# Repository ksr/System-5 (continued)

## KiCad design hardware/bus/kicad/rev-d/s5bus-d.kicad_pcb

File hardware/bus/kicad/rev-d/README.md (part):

# System-5 bus backplane Rev D (S5BUS-D): KiCad master

A fresh backplane (2026-10-26), derived from the cards that plug in and from the board Ken built in 2009
(`../rev-2009/`, six 36-pin slots). Generated by `gen/` from one netlist (`gen/netlist.py`): `gen/make_schematic.py`
writes the schematic, `gen/make_board.py` the board; Freerouting routes what the generator does not lay itself.

**Not ordered.** Before any order: `~/Developer/pcb-check/pcb-check hardware/bus/kicad/rev-d/s5bus-d.kicad_pcb hardware/bus/kicad/rev-d/s5bus-d-gerbers.zip --layers 2` must show no FAIL (Ken's check for every system since 2026-11-06; `hardware/BUILD-RULES.md`, section 2). **Power redone on 2026-11-18** (Ken: "simplify bus power"): a barrel jack for any 7–15 V adapter, a Schottky against a reversed plug, the power switch and a 3 A switching regulator, no fuse, in place of the screw terminal for a 5 V supply, the polyfuse and the P-MOSFET; the values of C2-C9 on the silkscreen (`pcb-check`'s one warning of 2026-11-16 and 17). Built by `gen/build.sh` (schematic, ERC, board, Freerouting on a fixed-order input, DRC, order files, `tools/preorder_check.py`): every build gives the same tracks. Since then: `tools/preorder_check.py --layers 2` PASS (DRC 0 errors and 0 warnings, the netlist proof 40 of 40); `pcb-check --tests` with `pcb-check.ini` (all eight slots against the bus definition; the bring-up tests) at elf `c2e90ac`: **no failures, 0 warnings**. **Then an external 5 V option** (Ken, the same evening): J10, two screw terminals for a regulated 5 V supply, and JP1, one jumper picking the source (REG or EXT), with the power switch after it for either source; `tools/preorder_check.py --layers 2` PASS (DRC 0 errors and 0 warnings, the netlist proof 42 of 42) and `pcb-check --tests` at elf `709855c`: **no failures, 0 warnings**. **Then, still on 2026-11-18, the slot and the board** (Ken): the 30-pin bus flush with each slot's GND end, the six extra lines beyond +5V, and the slot counted from GND ("The slot" below); RN2 9 mm further from slot 1's socket; 1.25 in between slots 7 and 8; the power switch a Marquardt 9070-1W, YACC1's RESET/RUN model; 2 mm more height at the GND end, 244.35 × 116 mm; `s5bus-d-1to1.pdf`. `tools/preorder_check.py --layers 2` PASS and `pcb-check --tests` at elf `31c54a8` (pcb-check `60fd275`, 2026-11-18): **no failures, 0 warnings** (the bus pins of all eight slots as defined, 288; 244.5 × 116.1 mm, 8 mounting holes; the bring-up tests pass). **Then the power switch again** (Ken, the same evening): an M9040P, the upright toggle of the IO panel's data switches, in place of the 9070-1W ("Circuit", SW1, with what is known of its rating); the supply feeds 2.0 mm into it again. `tools/preorder_check.py --layers 2` PASS (DRC 0 errors and 0 warnings, 0 unconnected, the netlist proof 42 of 42; routing seed 0) and `pcb-check --tests` at elf `4b24853` (2026-11-18, by the pcb-check session): **no failures, 0 warnings**. **Then, 2026-11-19, SW1's body on the fab layer at full size** (Ken: "yes draw the toggle outline full size"; a drawing only: no pad, label or track changed, the copper and the silkscreen checked the same): `tools/preorder_check.py --layers 2` PASS and `pcb-check --tests` at elf `e5322e4` (pcb-check `f93259d`): **no failures, 0 warnings**, every text clear of the parts with the toggle at its true size. SW1's part number is still to be read off the switch that will be fitted, for its rating ("Circuit", SW1).

## Ken's choices (2026-10-26)

| Choice | Decision |
|---|---|
| Pins per slot | **36**, as 2009. Since 2026-11-18 the 30-pin bus ends at the slot's end pin, GND, and a 30-pin card plugs in flush with that end (below); until then it took the middle 30, as on the 2009 board |
| Slots | **8** (CPU, memory, 6845, IO, IDE, bus driver, two spare) |
| Slot spacing (2026-11-18) | **1.0 in (25.4 mm)**, as 2009, **but 1.25 in (31.75 mm) between slots 7 and 8**, the two farthest from the power connector (Ken: "only that one space"): slot 8's card has 27.6 mm for its components instead of 21.3 (the board 6.35 mm wider, 244.35 mm) |
| Height (2026-11-18) | **116 mm**, 2 mm more at the GND end (Ken), so a 30-pin card plugged in flush with that end stays over the board |
| Power (2026-11-18) | **a centre-positive barrel jack for any 7–15 V adapter, a Schottky diode against a reversed plug, the power switch, a 3 A switching regulator to 5 V, the power LED; no fuse** (Ken: "simplify bus power"). Until then: a screw terminal for a 5 V supply and no regulator, as built in 2009 |
| External 5 V (2026-11-18) | **or an external regulated 5 V supply on two screw terminals (J10), the source picked by one 3-pin jumper (JP1): REG, the regulator, or EXT, J10; the power switch after the jumper, so it switches either source** (Ken: "add an option that 5V can also come from an external regulated supply. Add jumpers to select source"; "External 5V will come in via 2 screw terminals"; his choices: one 3-pin jumper, whose single shunt cannot join the two supplies, and the switch after it) |
| Pull-ups | 10k on D0–D7 and on the open-collector lines -EF, -EF1–3, -PAUSE, -DMAIN; -INT and -RESET added 2026-10-31 |
| Idle states (2026-11-01) | 10k pull-downs on N0–N2, TPA, TPB and pull-ups on -VMA, -MRD, -MRW: with no master on the bus, no I/O port is selected, no strobe is active and no card drives the data lines or writes memory |
| Mounting holes | 8 × M3, **four along each long edge**, between slots |
| Review fixes (2026-10-26) | copper keep-outs at the holes, 2.5 mm supply feeds, a card-window bracket on each slot (below) |
| After the independent reviews (2026-10-27) | a 5 A power switch (E-Switch 100 series, right-angle), a 4 A polyfuse and a P-channel MOSFET for reverse-polarity protection (both gone with the barrel jack, 2026-11-18), C1 in a 6.3 mm can, 1.0 mm silkscreen text, separate PTH / NPTH drill files |

## The slot

Pins are numbered by position along the 36-pin socket, **counted from the GND end** (the socket itself is an unnumbered
strip: the numbers are the drawings', and each socket's footprint is turned so that its pin 1 is that end). **The order
since 2026-11-18** (Ken: "looking at the bus from the power supply end I want the right most pin to be gnd followed by
the next original pin order all the way to +5v/vcc, then EF1, EF2, EF3, -DMAin, SC0", -PAUSE kept, at the far end; and
"start counting at gnd as pin 1, there +5v is 30 and then the pins beyond 5v"):

| Positions | Lines |
|---|---|
| 1–30 | the 30-pin System-5 bus from its GND end: GND at 1, the end pin (the rightmost, seen from the power connector), N0 2, N1 3, -RESET 4, -VMA 5, -EF 6, N2 7, -INT 8, A7–A0 at 9–16, -MRW 17, -MRD 18, TPB 19, TPA 20, Q 21, D7–D0 at 22–29, +5V at 30. A 30-pin card's own pin *n* (+5V 1 … GND 30) is position 31 − *n* |
| 31–33 | -EF1, -EF2, -EF3 (-EF1 next to +5V) |
| 34–36 | -DMAIN, SC0, -PAUSE (-PAUSE at the far end: the leftmost, seen from the power connector) |

A 30-pin card plugs into positions 1–30, flush with the GND end. Until 2026-11-18 the slot was counted from the other
end, in the 2009 board's order: 1–3 -EF1, -EF2, -EF3, 4–33 the 30-pin bus (+5V at 4, GND at 33), 34–36 -PAUSE, -DMAIN,
SC0 (the 2009 drawing's -INP, -OUT, EXP), the 30-pin bus in the middle. So a 36-pin card for this order (CPU Rev D, the
IO panel, BUSDRV-C) **does not fit the 2009 backplane**: there its +5V pin would meet D2. A 30-pin card fits both. The
2009 board's Eagle pin numbers differ too (1–30 the bus, 31–33 -EF1–3, 34–36 the rest), and its copper wired -EF1 next
to +5V, as here now, although its silkscreen says -EF3. The bus lines themselves, the pull-ups and the slots' places
are as before: only which line runs along which row changed, with RN1 (in line with the +5V and D0–D7 rows) and the
card-window brackets, and RN3 and RN4 moved to make room for RN1.

## Circuit

| Part | What |
|---|---|
| J1–J8 | the slots: 36-pin single-row 0.1" sockets on a 1.0" (25.4 mm) pitch, as 2009, but slots 7 and 8 1.25" (31.75 mm) apart (Ken, 2026-11-18) |
| J9 | power in: a DC barrel jack, Same Sky (formerly CUI) **PJ-063AH** (right angle, 2.0 mm centre pin for the common 5.5 × 2.1 mm plug, 8 A, 24 V; Digi-Key and Mouser stock it), at the left edge with its opening flush with the edge. **Centre positive**, 7–15 V: a 9 V or 12 V adapter of 2 A or more is the usual choice (a 7 V one at most about 2 A of load: below). Pin 1 the centre pin, pin 2 the sleeve (GND); its two kinked support legs (MP) are soldered to GND. Labelled J9 POWER IN, 7-15V DC, CENTER + |
| D2 | reverse-polarity protection: a Schottky rectifier, Vishay **SB540-E3/54** (40 V, 5 A, DO-201AD; the onsemi SB540 is obsolete), in series from J9's centre pin, lying flat (5.3 mm body). A centre-negative plug leaves it reverse-biased, so nothing reaches C10, the regulator or the cards. It drops about 0.4 V at 2 A (about 0.8 W), which the regulator absorbs |
| C10 | 47 µF 35 V, 6.3 mm can, on the regulator's input side (after D2, so a reversed plug never reaches it): it damps the ring when an adapter is plugged in live, through its cable's inductance |
| SW1 | power switch: an **M9040P**, the upright Marquardt SPDT toggle of the IO panel's data switches and of the YACC1 IO card (Ken, 2026-11-18: "bus change on off switch to same toggle used on IO card data 1-8"; earlier that day a right-angle Marquardt 9070-1W, YACC1's RESET/RUN model, which a real switch fitted on the full-size print, and from 2026-10-27 an E-Switch 100 series). Footprint `s5bus.pretty/M9040P`, the IO panel's (the YACC1 IO card's, pad for pad): three oval pads 5.41 × 2.71 mm, 4.699 mm apart, 1.8 mm holes (its body's outline on the fab layer at full size since 2026-11-19, Ken: "yes draw the toggle outline full size"; until then that layer had only the sketch of the lever, 8.2 × 10.3 mm); a body of 8.6 × 13.4 mm standing on the board below J10, 10.9 mm in from the left edge, its lever moving along that edge. It follows the source jumper and switches whichever source JP1 picks: common (pin 2) from JP1's middle pin; pin 3 to +5V = ON with the lever **up**, towards J9 (a toggle closes the contact on the side away from its lever: check against a real switch); pin 1 open = OFF. U1 runs whenever an adapter is in J9, the switch only cutting its output from the bus. Labelled ON, SW1 POWER and OFF beside it, each position level with the end its lever is at. **Its contact rating:** the whole bus current passes through it (up to 3 A from U1, or what J10's supply gives). Distributors list Marquardt's standard 9040-series toggles at 5 A 48 V AC and about 4 A 30 V DC, which covers it; the series' low-level (gold contact) versions are for 0.4 VA only and would not do. The data sheets themselves could not be read here on 2026-11-18: check the part number on the switch that is fitted |
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
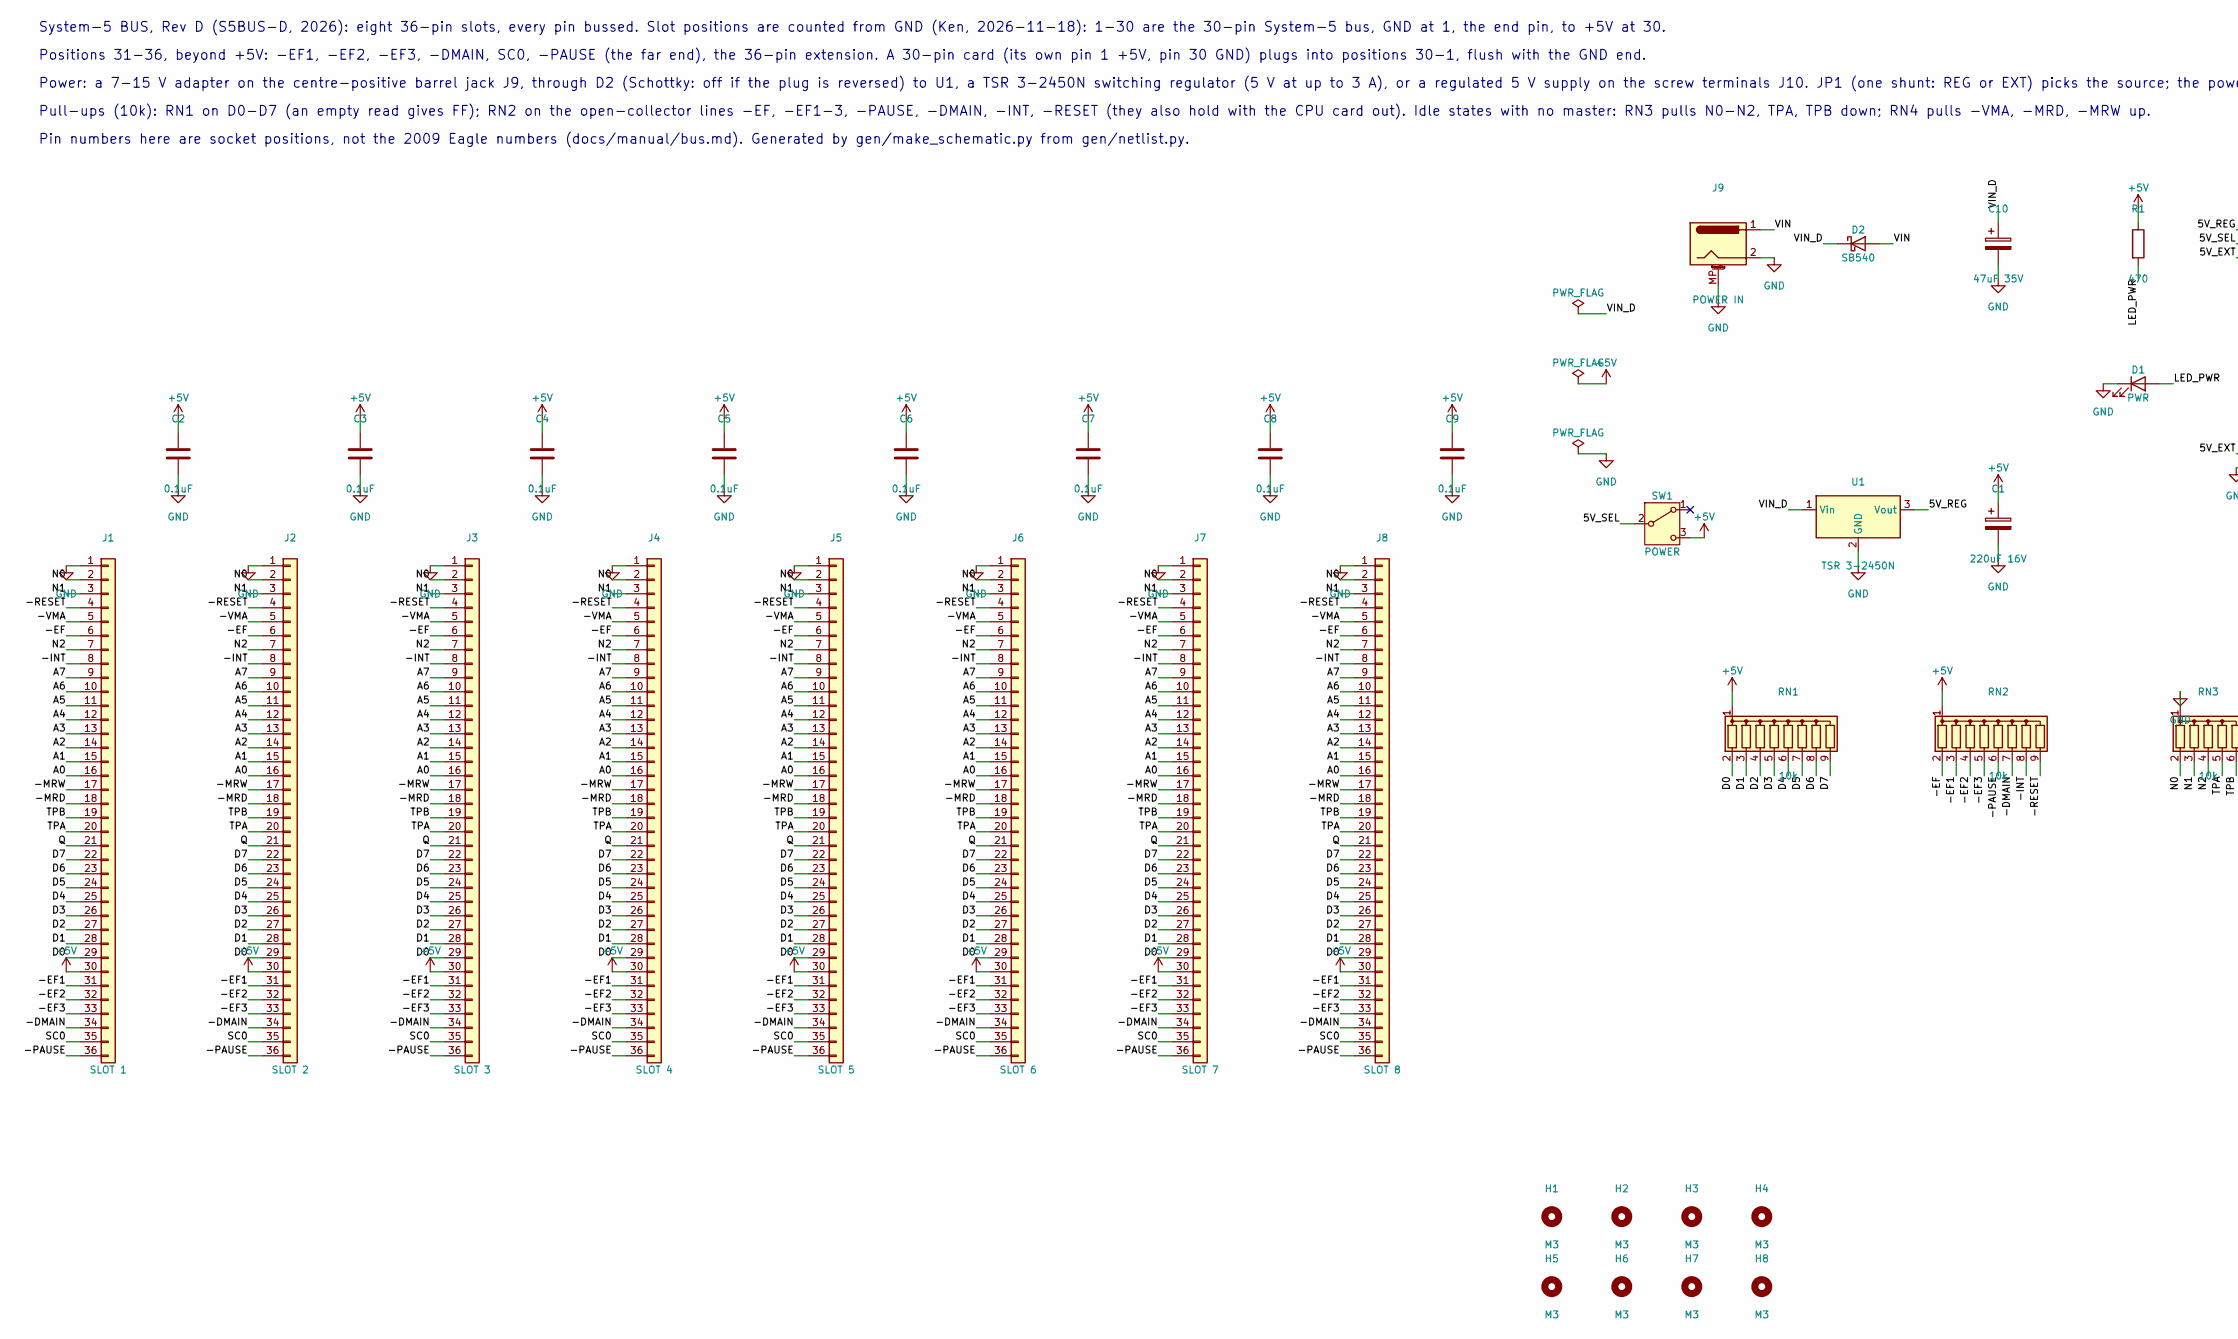
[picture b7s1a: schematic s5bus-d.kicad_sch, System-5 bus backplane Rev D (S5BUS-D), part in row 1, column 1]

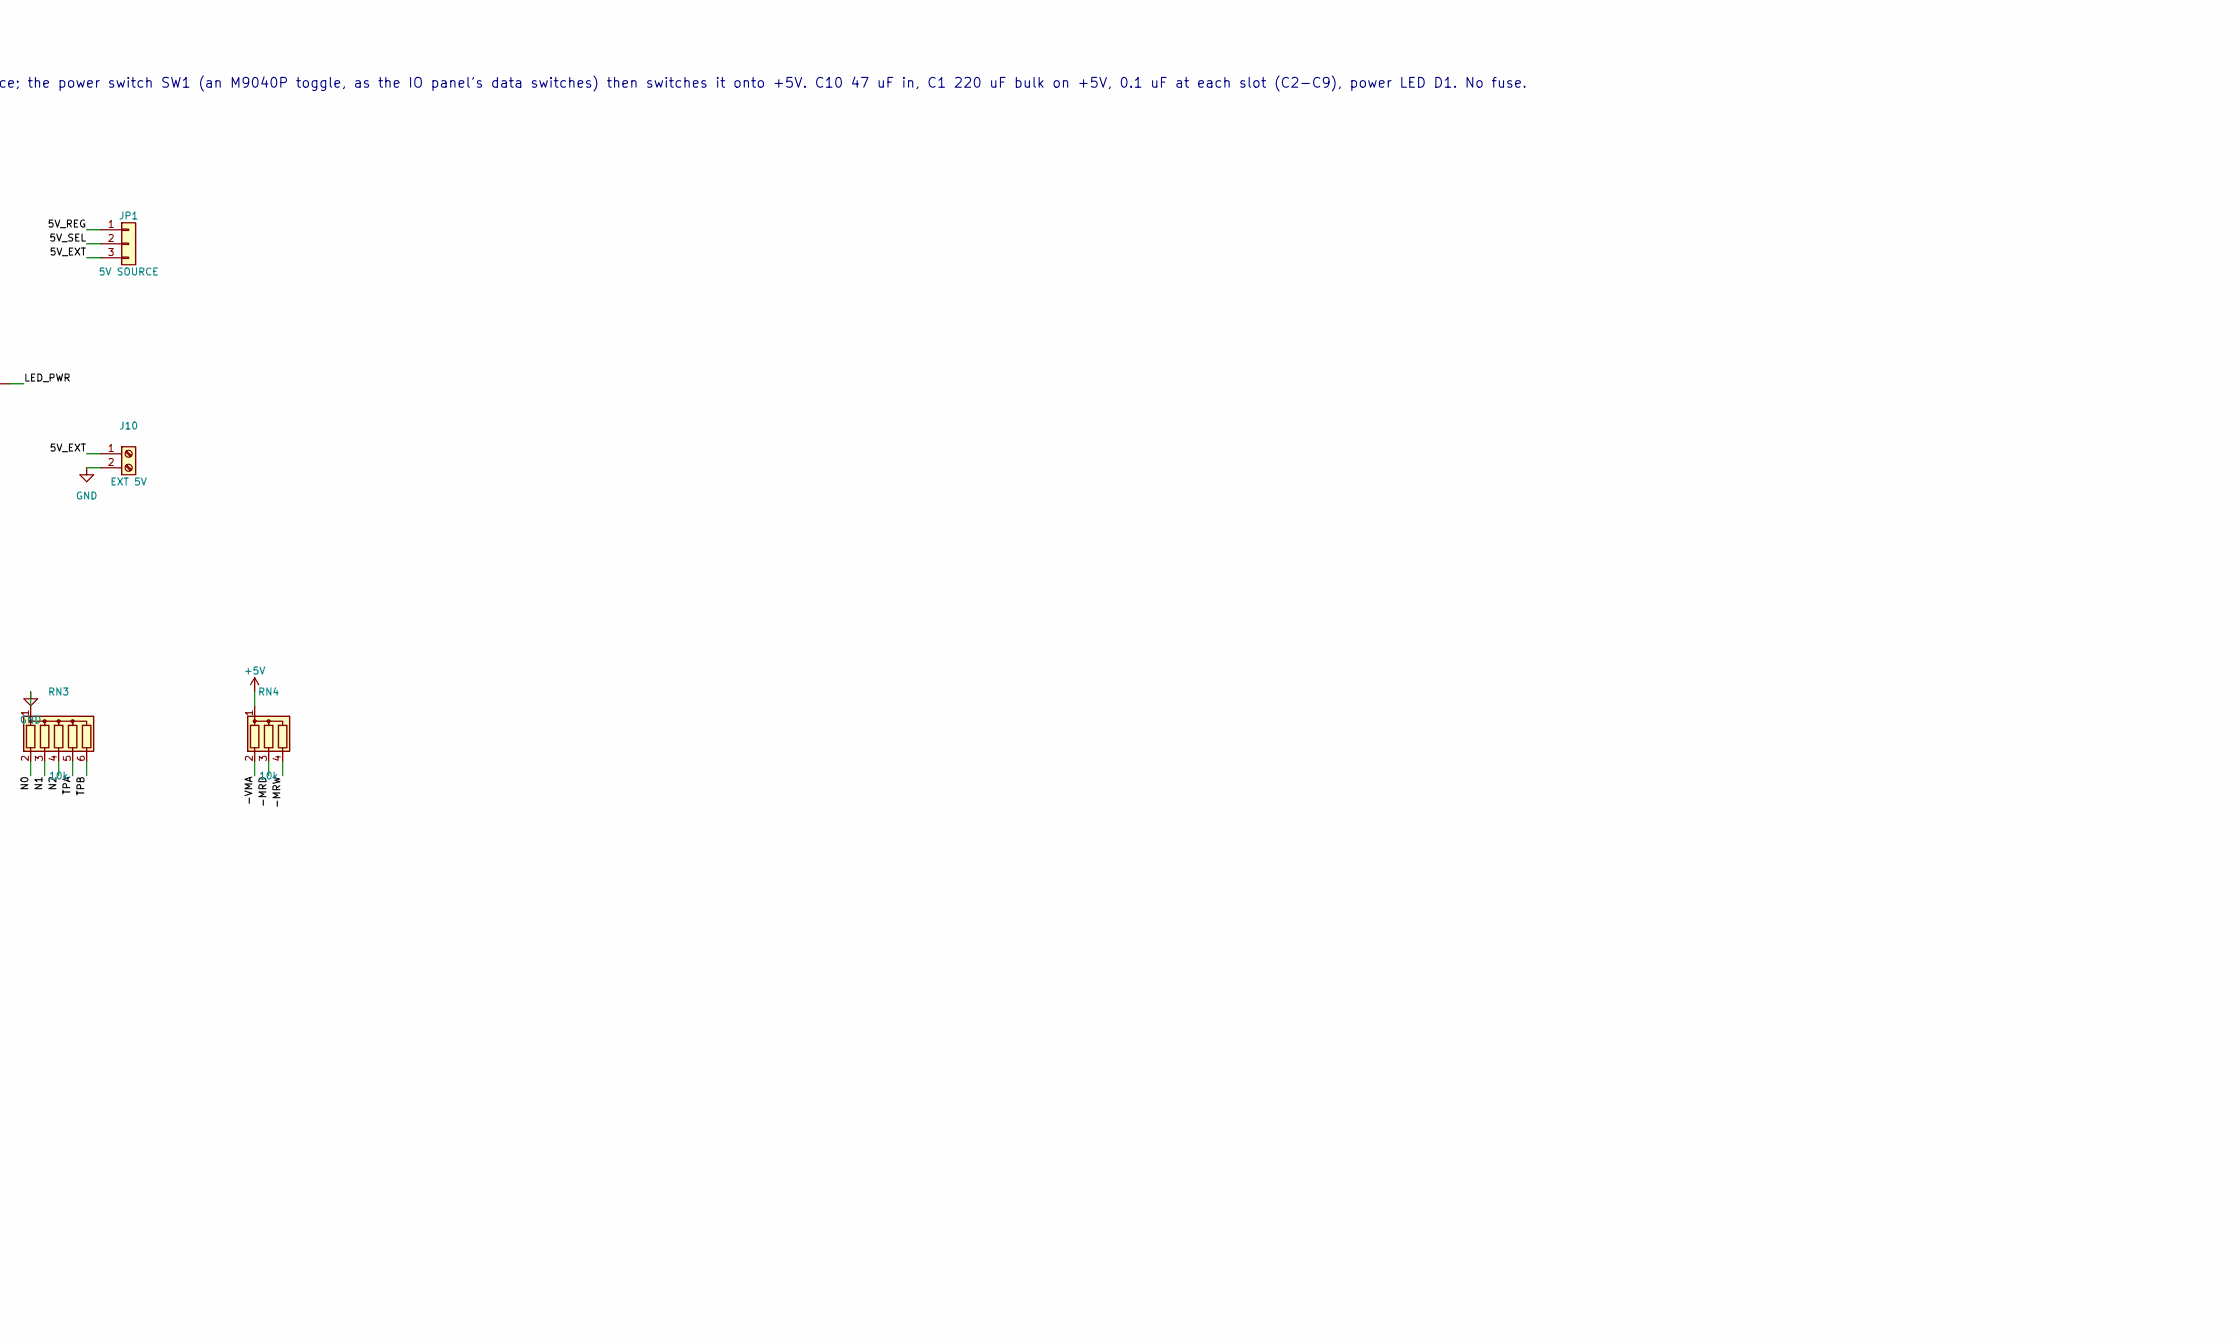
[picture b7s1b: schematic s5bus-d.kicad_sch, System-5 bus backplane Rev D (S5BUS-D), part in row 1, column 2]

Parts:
C1: 220uF 16V; CP_Radial_D6.3mm_P2.50mm
C2, C3, C4, C5, C6, C7, C8, C9: 0.1uF; C025-050X050
C10: 47uF 35V; CP_Radial_D6.3mm_P2.50mm
D1: PWR; LED_D5.0mm
D2: SB540; D_DO-201AD_P15.24mm_Horizontal
H1, H2, H3, H4, H5, H6, H7, H8: M3; MountingHole_3.2mm_M3
J1: SLOT 1; PinSocket_1x36_P2.54mm_Vertical
J2: SLOT 2; PinSocket_1x36_P2.54mm_Vertical
J3: SLOT 3; PinSocket_1x36_P2.54mm_Vertical
J4: SLOT 4; PinSocket_1x36_P2.54mm_Vertical
J5: SLOT 5; PinSocket_1x36_P2.54mm_Vertical
J6: SLOT 6; PinSocket_1x36_P2.54mm_Vertical
J7: SLOT 7; PinSocket_1x36_P2.54mm_Vertical
J8: SLOT 8; PinSocket_1x36_P2.54mm_Vertical
J9: POWER IN; BarrelJack_CUI_PJ-063AH_Horizontal
J10: EXT 5V; TerminalBlock_Phoenix_MKDS-1,5-2-5.08_1x02_P5.08mm_Horizont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
JP1: 5V SOURCE; PinHeader_1x03_P2.54mm_Vertical
R1: 470; R_Axial_DIN0207_L6.3mm_D2.5mm_P7.62mm_Horizontal
RN1, RN2: 10k; R_Array_SIP9
RN3: 10k; R_Array_SIP6
RN4: 10k; R_Array_SIP4
SW1: POWER; M9040P
U1: TSR 3-2450N; Converter_DCDC_TRACO_TSR2-24xxN_TSR2-24xxxN_THT

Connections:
+5V: C1.1, C2.1, C3.1, C4.1, C5.1, C6.1, C7.1, C8.1, C9.1, J1.30, J2.30, J3.30, J4.30, J5.30, J6.30, J7.30, J8.30, R1.1, RN1.1 (common), RN2.1 (common), RN4.1 (common), SW1.3 (C)
/5V_EXT: J10.1, JP1.3
/5V_REG: JP1.1, U1.3 (Vout)
/5V_SEL: JP1.2, SW1.2 (B)
/-DMAIN: J1.34, J2.34, J3.34, J4.34, J5.34, J6.34, J7.34, J8.34, RN2.7 (R6)
/-EF: J1.6, J2.6, J3.6, J4.6, J5.6, J6.6, J7.6, J8.6, RN2.2 (R1)
/-EF1: J1.31, J2.31, J3.31, J4.31, J5.31, J6.31, J7.31, J8.31, RN2.3 (R2)
/-EF2: J1.32, J2.32, J3.32, J4.32, J5.32, J6.32, J7.32, J8.32, RN2.4 (R3)
/-EF3: J1.33, J2.33, J3.33, J4.33, J5.33, J6.33, J7.33, J8.33, RN2.5 (R4)
/-INT: J1.8, J2.8, J3.8, J4.8, J5.8, J6.8, J7.8, J8.8, RN2.8 (R7)
/-MRD: J1.18, J2.18, J3.18, J4.18, J5.18, J6.18, J7.18, J8.18, RN4.3 (R2)
/-MRW: J1.17, J2.17, J3.17, J4.17, J5.17, J6.17, J7.17, J8.17, RN4.4 (R3)
/-PAUSE: J1.36, J2.36, J3.36, J4.36, J5.36, J6.36, J7.36, J8.36, RN2.6 (R5)
/-RESET: J1.4, J2.4, J3.4, J4.4, J5.4, J6.4, J7.4, J8.4, RN2.9 (R8)
/-VMA: J1.5, J2.5, J3.5, J4.5, J5.5, J6.5, J7.5, J8.5, RN4.2 (R1)
/A0: J1.16, J2.16, J3.16, J4.16, J5.16, J6.16, J7.16, J8.16
/A1: J1.15, J2.15, J3.15, J4.15, J5.15, J6.15, J7.15, J8.15
/A2: J1.14, J2.14, J3.14, J4.14, J5.14, J6.14, J7.14, J8.14
/A3: J1.13, J2.13, J3.13, J4.13, J5.13, J6.13, J7.13, J8.13
/A4: J1.12, J2.12, J3.12, J4.12, J5.12, J6.12, J7.12, J8.12
/A5: J1.11, J2.11, J3.11, J4.11, J5.11, J6.11, J7.11, J8.11
/A6: J1.10, J2.10, J3.10, J4.10, J5.10, J6.10, J7.10, J8.10
/A7: J1.9, J2.9, J3.9, J4.9, J5.9, J6.9, J7.9, J8.9
/D0: J1.29, J2.29, J3.29, J4.29, J5.29, J6.29, J7.29, J8.29, RN1.2 (R1)
/D1: J1.28, J2.28, J3.28, J4.28, J5.28, J6.28, J7.28, J8.28, RN1.3 (R2)
/D2: J1.27, J2.27, J3.27, J4.27, J5.27, J6.27, J7.27, J8.27, RN1.4 (R3)
/D3: J1.26, J2.26, J3.26, J4.26, J5.26, J6.26, J7.26, J8.26, RN1.5 (R4)
/D4: J1.25, J2.25, J3.25, J4.25, J5.25, J6.25, J7.25, J8.25, RN1.6 (R5)
/D5: J1.24, J2.24, J3.24, J4.24, J5.24, J6.24, J7.24, J8.24, RN1.7 (R6)
/D6: J1.23, J2.23, J3.23, J4.23, J5.23, J6.23, J7.23, J8.23, RN1.8 (R7)
/D7: J1.22, J2.22, J3.22, J4.22, J5.22, J6.22, J7.22, J8.22, RN1.9 (R8)
/LED_PWR: D1.2 (A), R1.2
/N0: J1.2, J2.2, J3.2, J4.2, J5.2, J6.2, J7.2, J8.2, RN3.2 (R1)
/N1: J1.3, J2.3, J3.3, J4.3, J5.3, J6.3, J7.3, J8.3, RN3.3 (R2)
/N2: J1.7, J2.7, J3.7, J4.7, J5.7, J6.7, J7.7, J8.7, RN3.4 (R3)
/Q: J1.21, J2.21, J3.21, J4.21, J5.21, J6.21, J7.21, J8.21
/SC0: J1.35, J2.35, J3.35, J4.35, J5.35, J6.35, J7.35, J8.35
/TPA: J1.20, J2.20, J3.20, J4.20, J5.20, J6.20, J7.20, J8.20, RN3.5 (R4)
/TPB: J1.19, J2.19, J3.19, J4.19, J5.19, J6.19, J7.19, J8.19, RN3.6 (R5)
/VIN: D2.2 (A), J9.1
/VIN_D: C10.1, D2.1 (K), U1.1 (Vin)
GND: C1.2, C2.2, C3.2, C4.2, C5.2, C6.2, C7.2, C8.2, C9.2, C10.2, D1.1 (K), J1.1, J2.1, J3.1, J4.1, J5.1, J6.1, J7.1, J8.1, J9.2, J9.MP (MountPin), J10.2, RN3.1 (common), U1.2 (GND)

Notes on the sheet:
System-5 BUS, Rev D (S5BUS-D, 2026): eight 36-pin slots, every pin bussed. Slot positions are counted from GND (Ken, 2026-11-18): 1-30 are the 30-pin System-5 bus, GND at 1, the end pin, to +5V at 30.
Positions 31-36, beyond +5V: -EF1, -EF2, -EF3, -DMAIN, SC0, -PAUSE (the far end), the 36-pin extension. A 30-pin card (its own pin 1 +5V, pin 30 GND) plugs into positions 30-1, flush with the GND end.
Power: a 7-15 V adapter on the centre-positive barrel jack J9, through D2 (Schottky: off if the plug is reversed) to U1, a TSR 3-2450N switching regulator (5 V at up to 3 A), or a regulated 5 V supply on the screw terminals J10. JP1 (one shunt: REG or EXT) picks the source; the power switch SW1 (an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
Pull-ups (10k): RN1 on D0-D7 (an empty read gives FF); RN2 on the open-collector lines -EF, -EF1-3, -PAUSE, -DMAIN, -INT, -RESET (they also hold with the CPU card out). Idle states with no master: RN3 pulls N0-N2, TPA, TPB down; RN4 pulls -VMA, -MRD, -MRW up.
Pin numbers here are socket positions, not the 2009 Eagle numbers (docs/manual/bus.md). Generated by gen/make_schematic.py from gen/netlist.py.

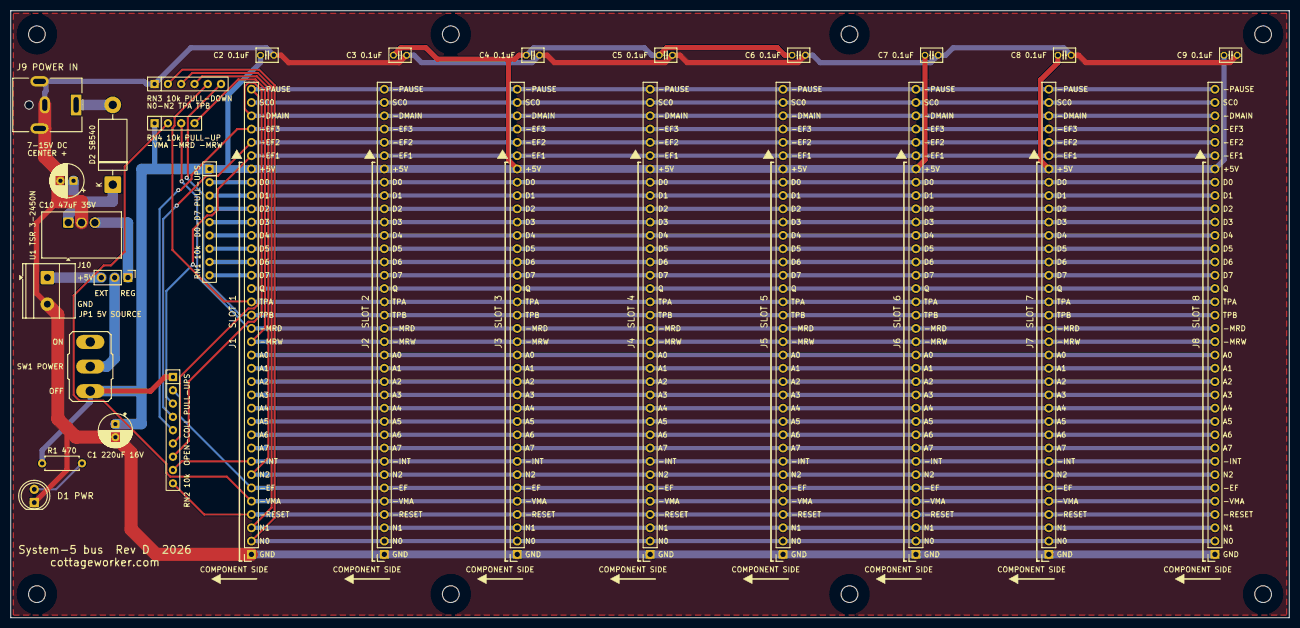
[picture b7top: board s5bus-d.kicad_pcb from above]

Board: 2 copper layers, 244.3 x 116.0 mm, 38 parts (0 on the bottom side), 42 nets.

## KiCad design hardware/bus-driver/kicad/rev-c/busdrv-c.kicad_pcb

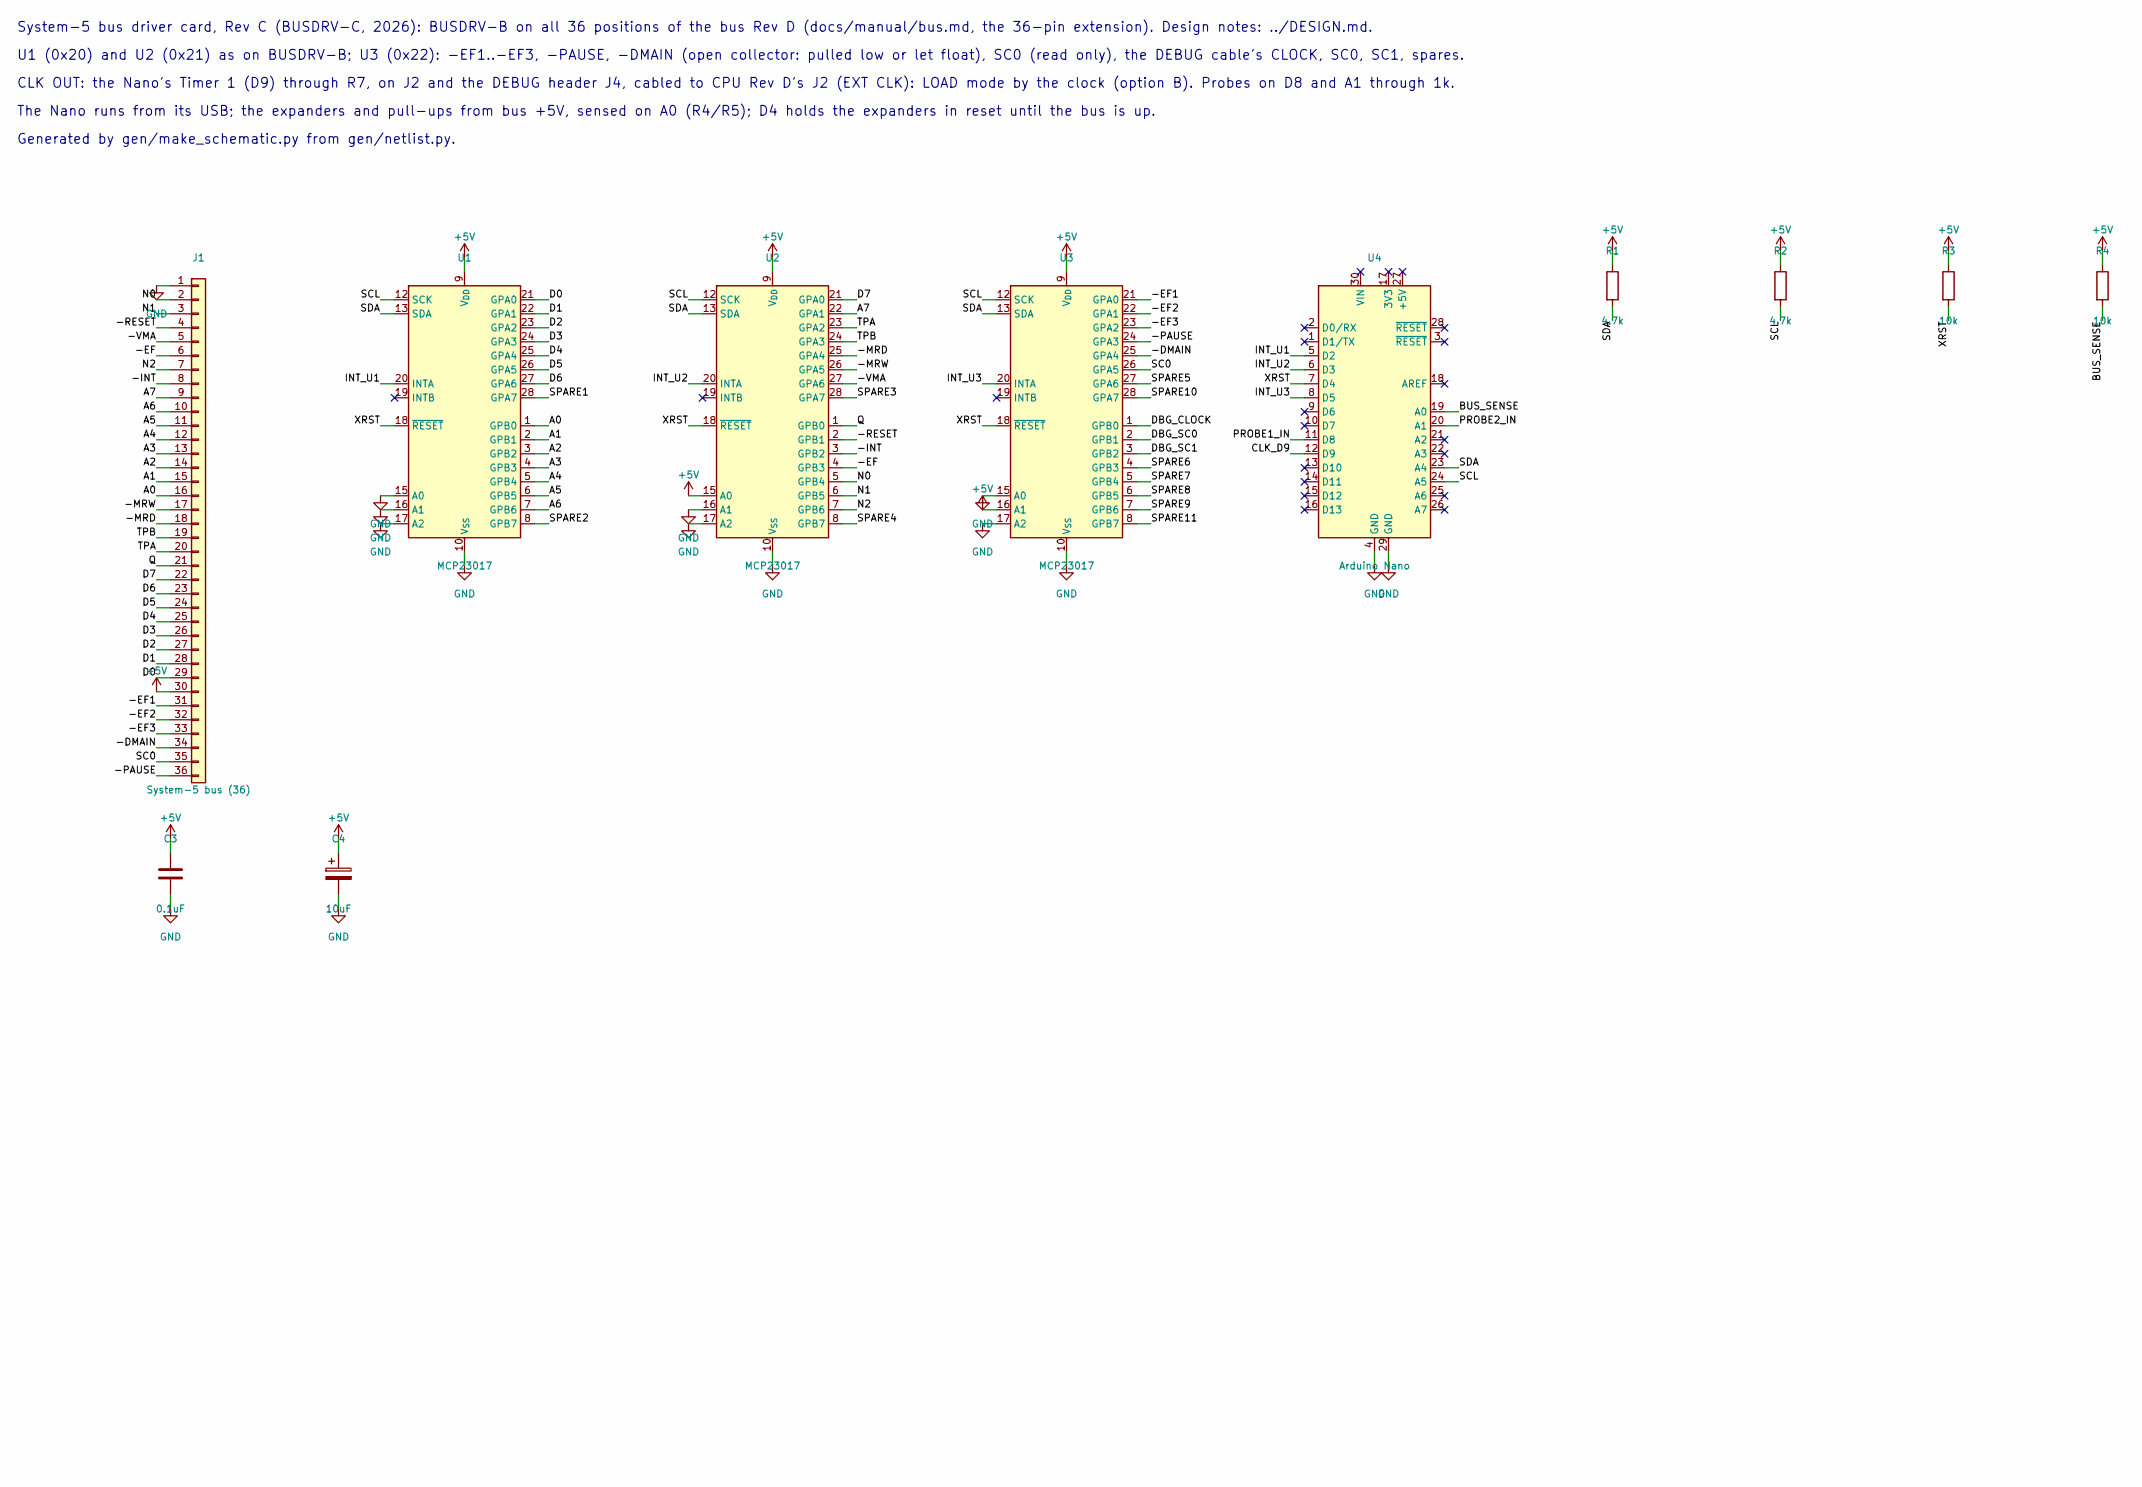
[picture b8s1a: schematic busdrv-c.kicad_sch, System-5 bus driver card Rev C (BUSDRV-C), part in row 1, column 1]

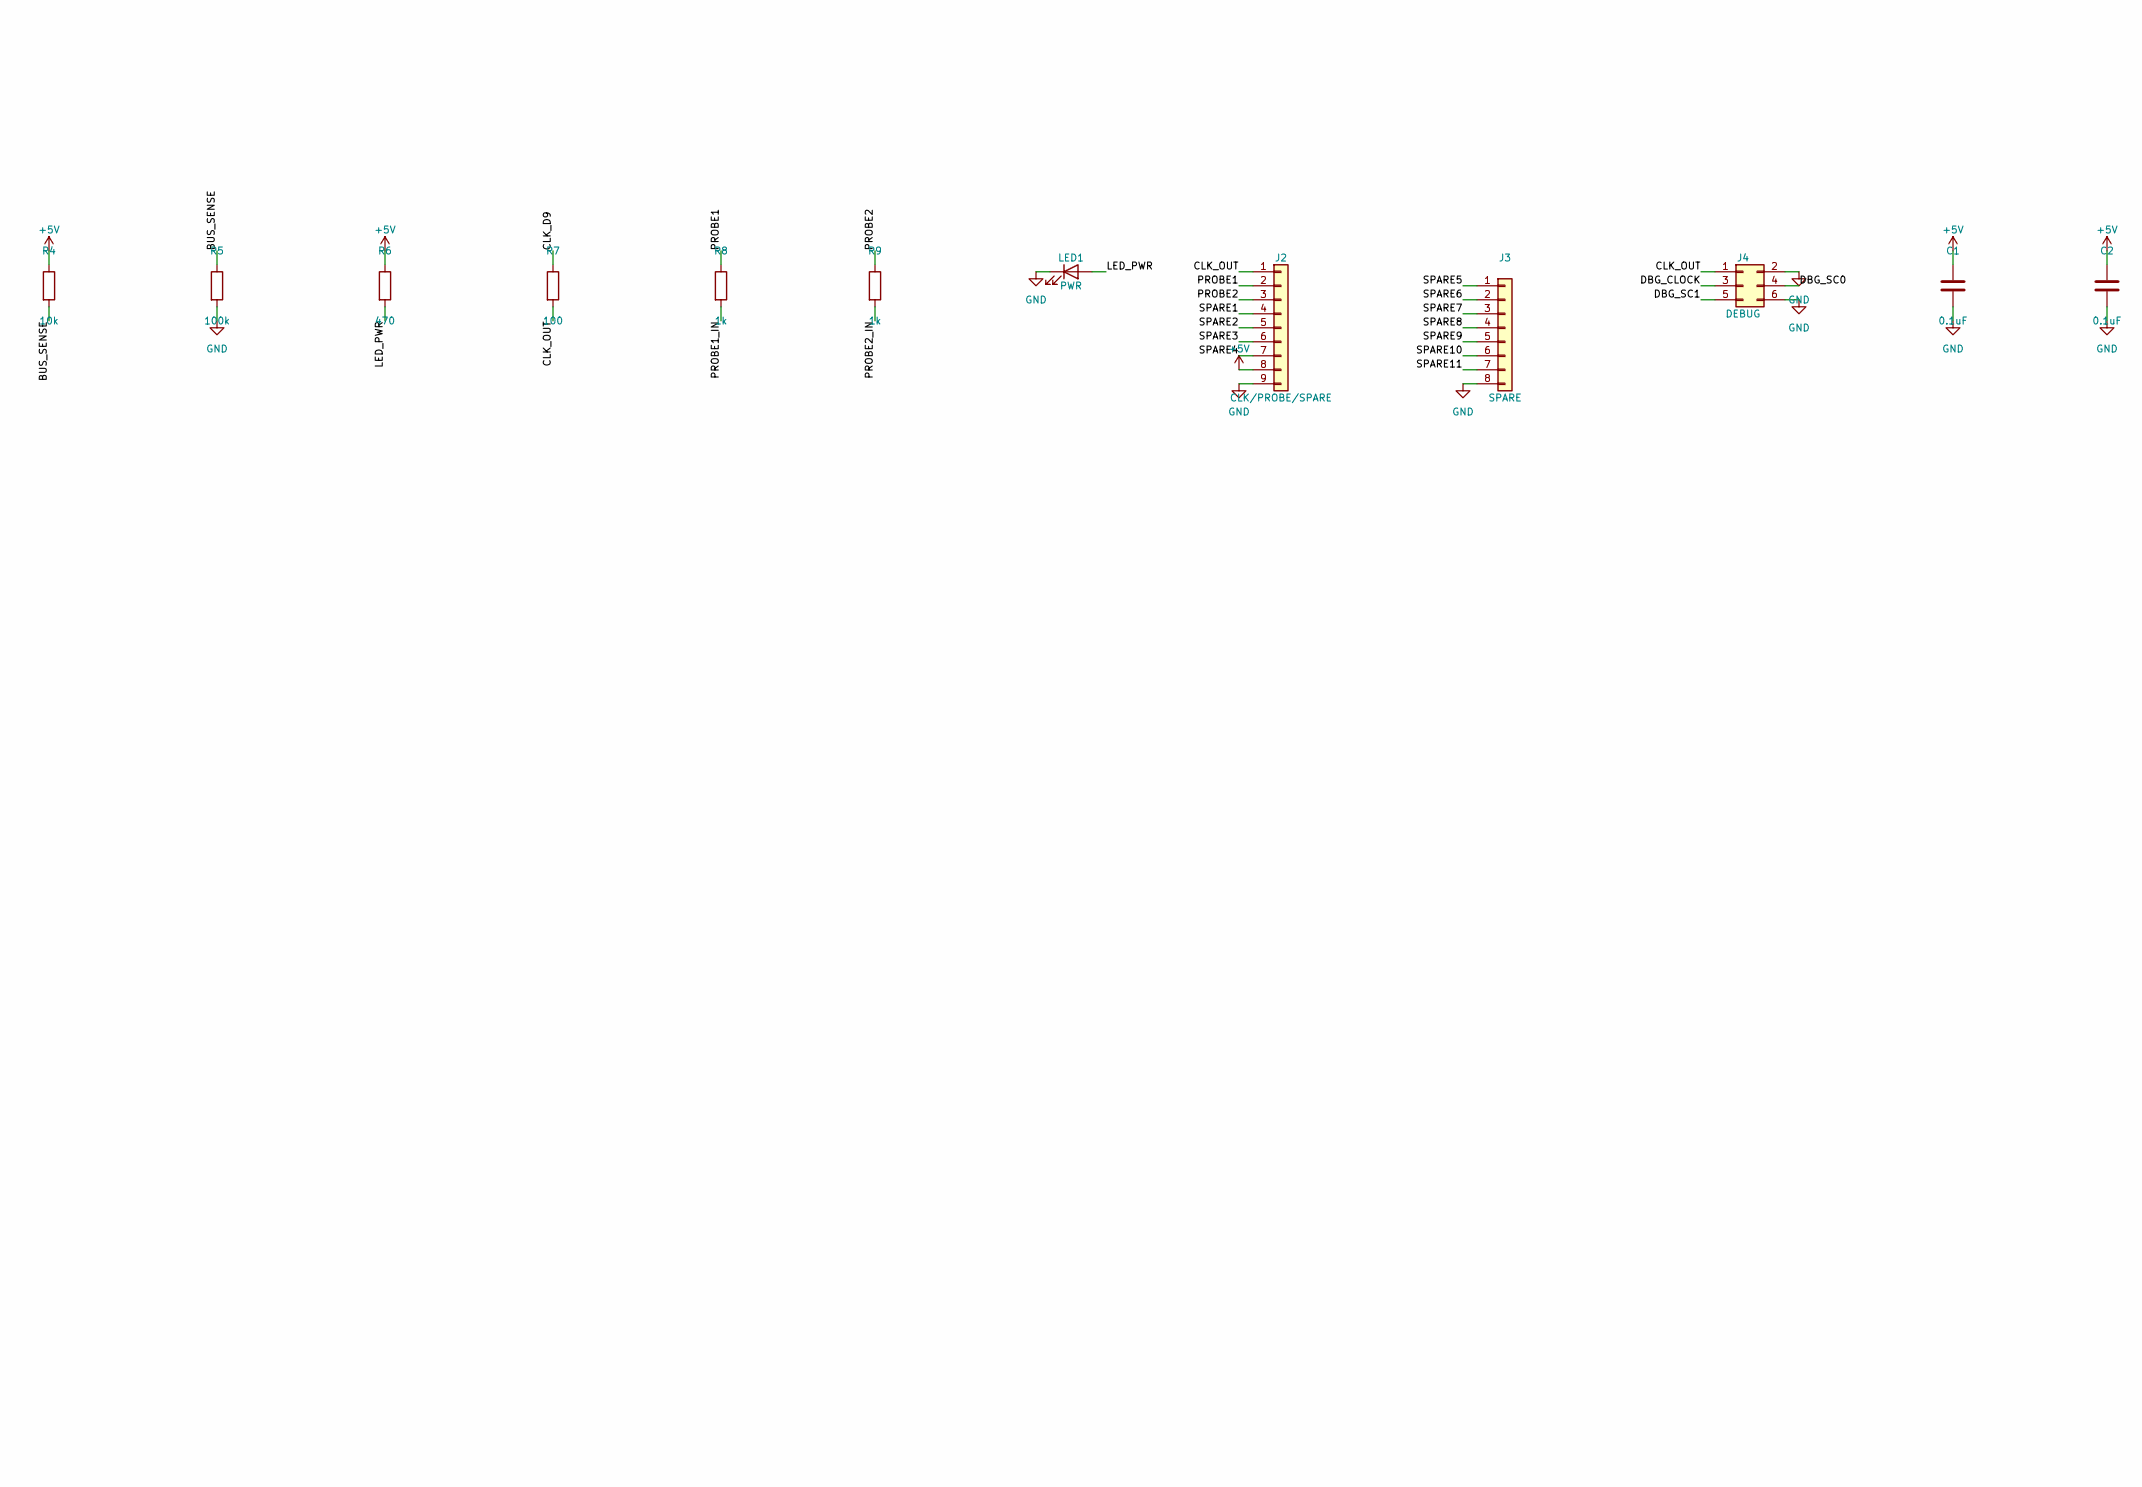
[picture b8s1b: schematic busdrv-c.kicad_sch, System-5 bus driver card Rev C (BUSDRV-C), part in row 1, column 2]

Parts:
C1, C2, C3: 0.1uF; C025-050X050
C4: 10uF; CP_Radial_D5.0mm_P2.00mm
J1: System-5 bus (36); C36
J2: CLK/PROBE/SPARE; PinHeader_1x09_P2.54mm_Vertical
J3: SPARE; PinHeader_1x08_P2.54mm_Vertical
J4: DEBUG; IDC-Header_2x03_P2.54mm_Vertical
LED1: PWR; LED_D3.0mm
R1, R2: 4.7k; R_Axial_DIN0207_L6.3mm_D2.5mm_P7.62mm_Horizontal
R3, R4: 10k; R_Axial_DIN0207_L6.3mm_D2.5mm_P7.62mm_Horizontal
R5: 100k; R_Axial_DIN0207_L6.3mm_D2.5mm_P7.62mm_Horizontal
R6: 470; R_Axial_DIN0207_L6.3mm_D2.5mm_P7.62mm_Horizontal
R7: 100; R_Axial_DIN0207_L6.3mm_D2.5mm_P7.62mm_Horizontal
R8, R9: 1k; R_Axial_DIN0207_L6.3mm_D2.5mm_P7.62mm_Horizontal
U1, U2, U3: MCP23017; DIP-28_W7.62mm
U4: Arduino Nano; Arduino_Nano

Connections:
+5V: C1.1, C2.1, C3.1, C4.1, J1.30, J2.8, R1.1, R2.1, R3.1, R4.1, R6.1, U1.9 (V_{DD}), U2.9 (V_{DD}), U2.15 (A0), U3.9 (V_{DD}), U3.16 (A1)
/-DMAIN: J1.34, U3.25 (GPA4)
/-EF: J1.6, U2.4 (GPB3)
/-EF1: J1.31, U3.21 (GPA0)
/-EF2: J1.32, U3.22 (GPA1)
/-EF3: J1.33, U3.23 (GPA2)
/-INT: J1.8, U2.3 (GPB2)
/-MRD: J1.18, U2.25 (GPA4)
/-MRW: J1.17, U2.26 (GPA5)
/-PAUSE: J1.36, U3.24 (GPA3)
/-RESET: J1.4, U2.2 (GPB1)
/-VMA: J1.5, U2.27 (GPA6)
/A0: J1.16, U1.1 (GPB0)
/A1: J1.15, U1.2 (GPB1)
/A2: J1.14, U1.3 (GPB2)
/A3: J1.13, U1.4 (GPB3)
/A4: J1.12, U1.5 (GPB4)
/A5: J1.11, U1.6 (GPB5)
/A6: J1.10, U1.7 (GPB6)
/A7: J1.9, U2.22 (GPA1)
/BUS_SENSE: R4.2, R5.1, U4.19 (A0)
/CLK_D9: R7.1, U4.12 (D9)
/CLK_OUT: J2.1, J4.1, R7.2
/D0: J1.29, U1.21 (GPA0)
/D1: J1.28, U1.22 (GPA1)
/D2: J1.27, U1.23 (GPA2)
/D3: J1.26, U1.24 (GPA3)
/D4: J1.25, U1.25 (GPA4)
/D5: J1.24, U1.26 (GPA5)
/D6: J1.23, U1.27 (GPA6)
/D7: J1.22, U2.21 (GPA0)
/DBG_CLOCK: J4.3, U3.1 (GPB0)
/DBG_SC0: J4.4, U3.2 (GPB1)
/DBG_SC1: J4.5, U3.3 (GPB2)
/INT_U1: U1.20 (INTA), U4.5 (D2)
/INT_U2: U2.20 (INTA), U4.6 (D3)
/INT_U3: U3.20 (INTA), U4.8 (D5)
/LED_PWR: LED1.2 (A), R6.2
/N0: J1.2, U2.5 (GPB4)
/N1: J1.3, U2.6 (GPB5)
/N2: J1.7, U2.7 (GPB6)
/PROBE1: J2.2, R8.1
/PROBE1_IN: R8.2, U4.11 (D8)
/PROBE2: J2.3, R9.1
/PROBE2_IN: R9.2, U4.20 (A1)
/Q: J1.21, U2.1 (GPB0)
/SC0: J1.35, U3.26 (GPA5)
/SCL: R2.2, U1.12 (SCK), U2.12 (SCK), U3.12 (SCK), U4.24 (A5)
/SDA: R1.2, U1.13 (SDA), U2.13 (SDA), U3.13 (SDA), U4.23 (A4)
/SPARE1: J2.4, U1.28 (GPA7)
/SPARE2: J2.5, U1.8 (GPB7)
/SPARE3: J2.6, U2.28 (GPA7)
/SPARE4: J2.7, U2.8 (GPB7)
/SPARE5: J3.1, U3.27 (GPA6)
/SPARE6: J3.2, U3.4 (GPB3)
/SPARE7: J3.3, U3.5 (GPB4)
/SPARE8: J3.4, U3.6 (GPB5)
/SPARE9: J3.5, U3.7 (GPB6)
/SPARE10: J3.6, U3.28 (GPA7)
/SPARE11: J3.7, U3.8 (GPB7)
/TPA: J1.20, U2.23 (GPA2)
/TPB: J1.19, U2.24 (GPA3)
/XRST: R3.2, U1.18 (~RESET), U2.18 (~RESET), U3.18 (~RESET), U4.7 (D4)
GND: C1.2, C2.2, C3.2, C4.2, J1.1, J2.9, J3.8, J4.2, J4.6, LED1.1 (K), R5.2, U1.10 (V_{SS}), U1.15 (A0), U1.16 (A1), U1.17 (A2), U2.10 (V_{SS}), U2.16 (A1), U2.17 (A2), U3.10 (V_{SS}), U3.15 (A0), U3.17 (A2), U4.4 (GND), U4.29 (GND)

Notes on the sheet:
System-5 bus driver card, Rev C (BUSDRV-C, 2026): BUSDRV-B on all 36 positions of the bus Rev D (docs/manual/bus.md, the 36-pin extension). Design notes: ../DESIGN.md.
U1 (0x20) and U2 (0x21) as on BUSDRV-B; U3 (0x22): -EF1..-EF3, -PAUSE, -DMAIN (open collector: pulled low or let float), SC0 (read only), the DEBUG cable's CLOCK, SC0, SC1, spares.
CLK OUT: the Nano's Timer 1 (D9) through R7, on J2 and the DEBUG header J4, cabled to CPU Rev D's J2 (EXT CLK): LOAD mode by the clock (option B). Probes on D8 and A1 through 1k.
The Nano runs from its USB; the expanders and pull-ups from bus +5V, sensed on A0 (R4/R5); D4 holds the expanders in reset until the bus is up.
Generated by gen/make_schematic.py from gen/netlist.py.

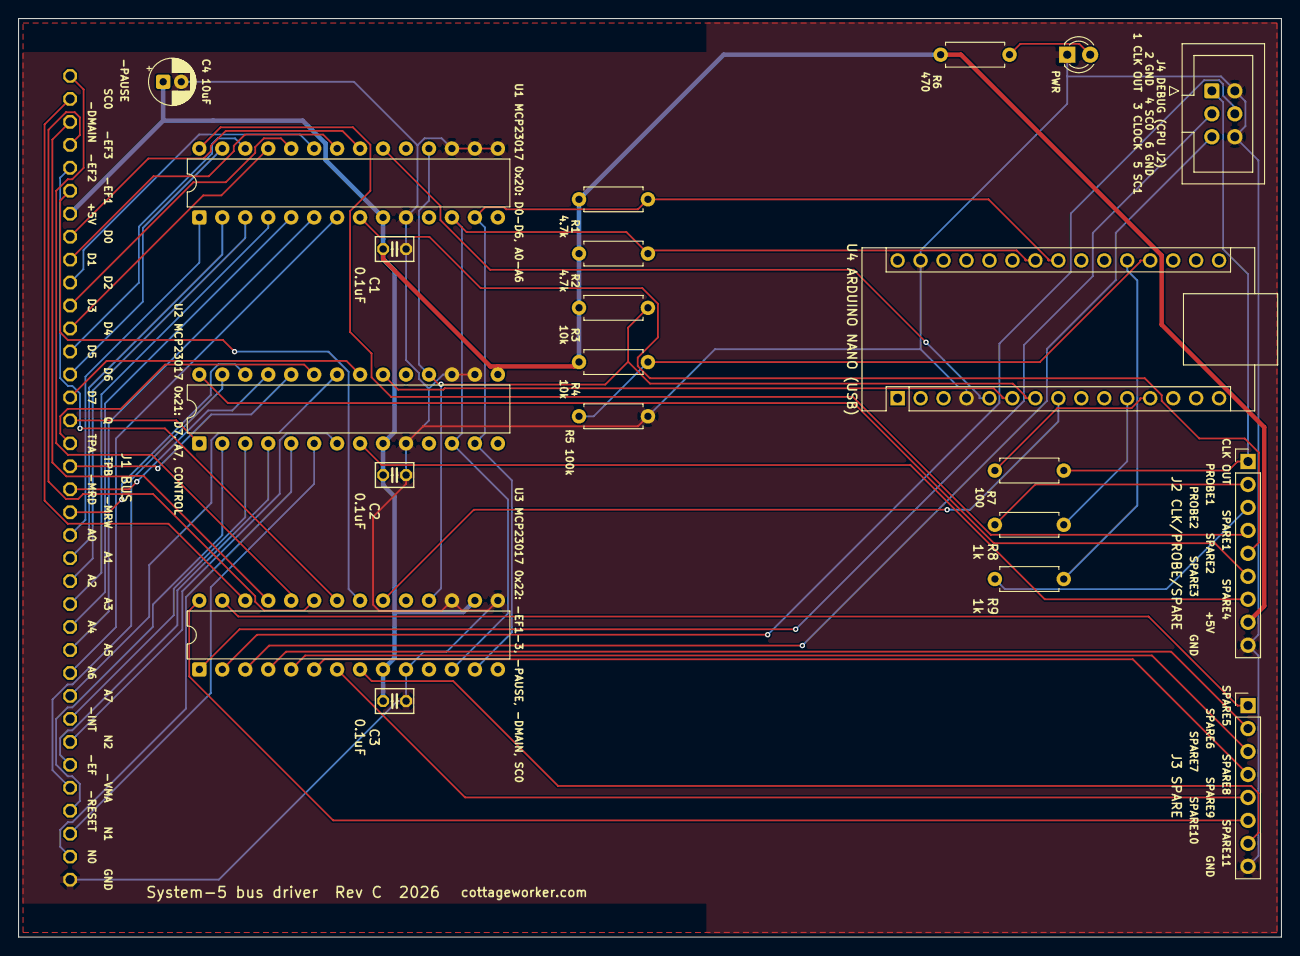
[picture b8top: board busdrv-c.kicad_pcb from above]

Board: 2 copper layers, 139.7 x 101.6 mm, 22 parts (0 on the bottom side), 64 nets.
